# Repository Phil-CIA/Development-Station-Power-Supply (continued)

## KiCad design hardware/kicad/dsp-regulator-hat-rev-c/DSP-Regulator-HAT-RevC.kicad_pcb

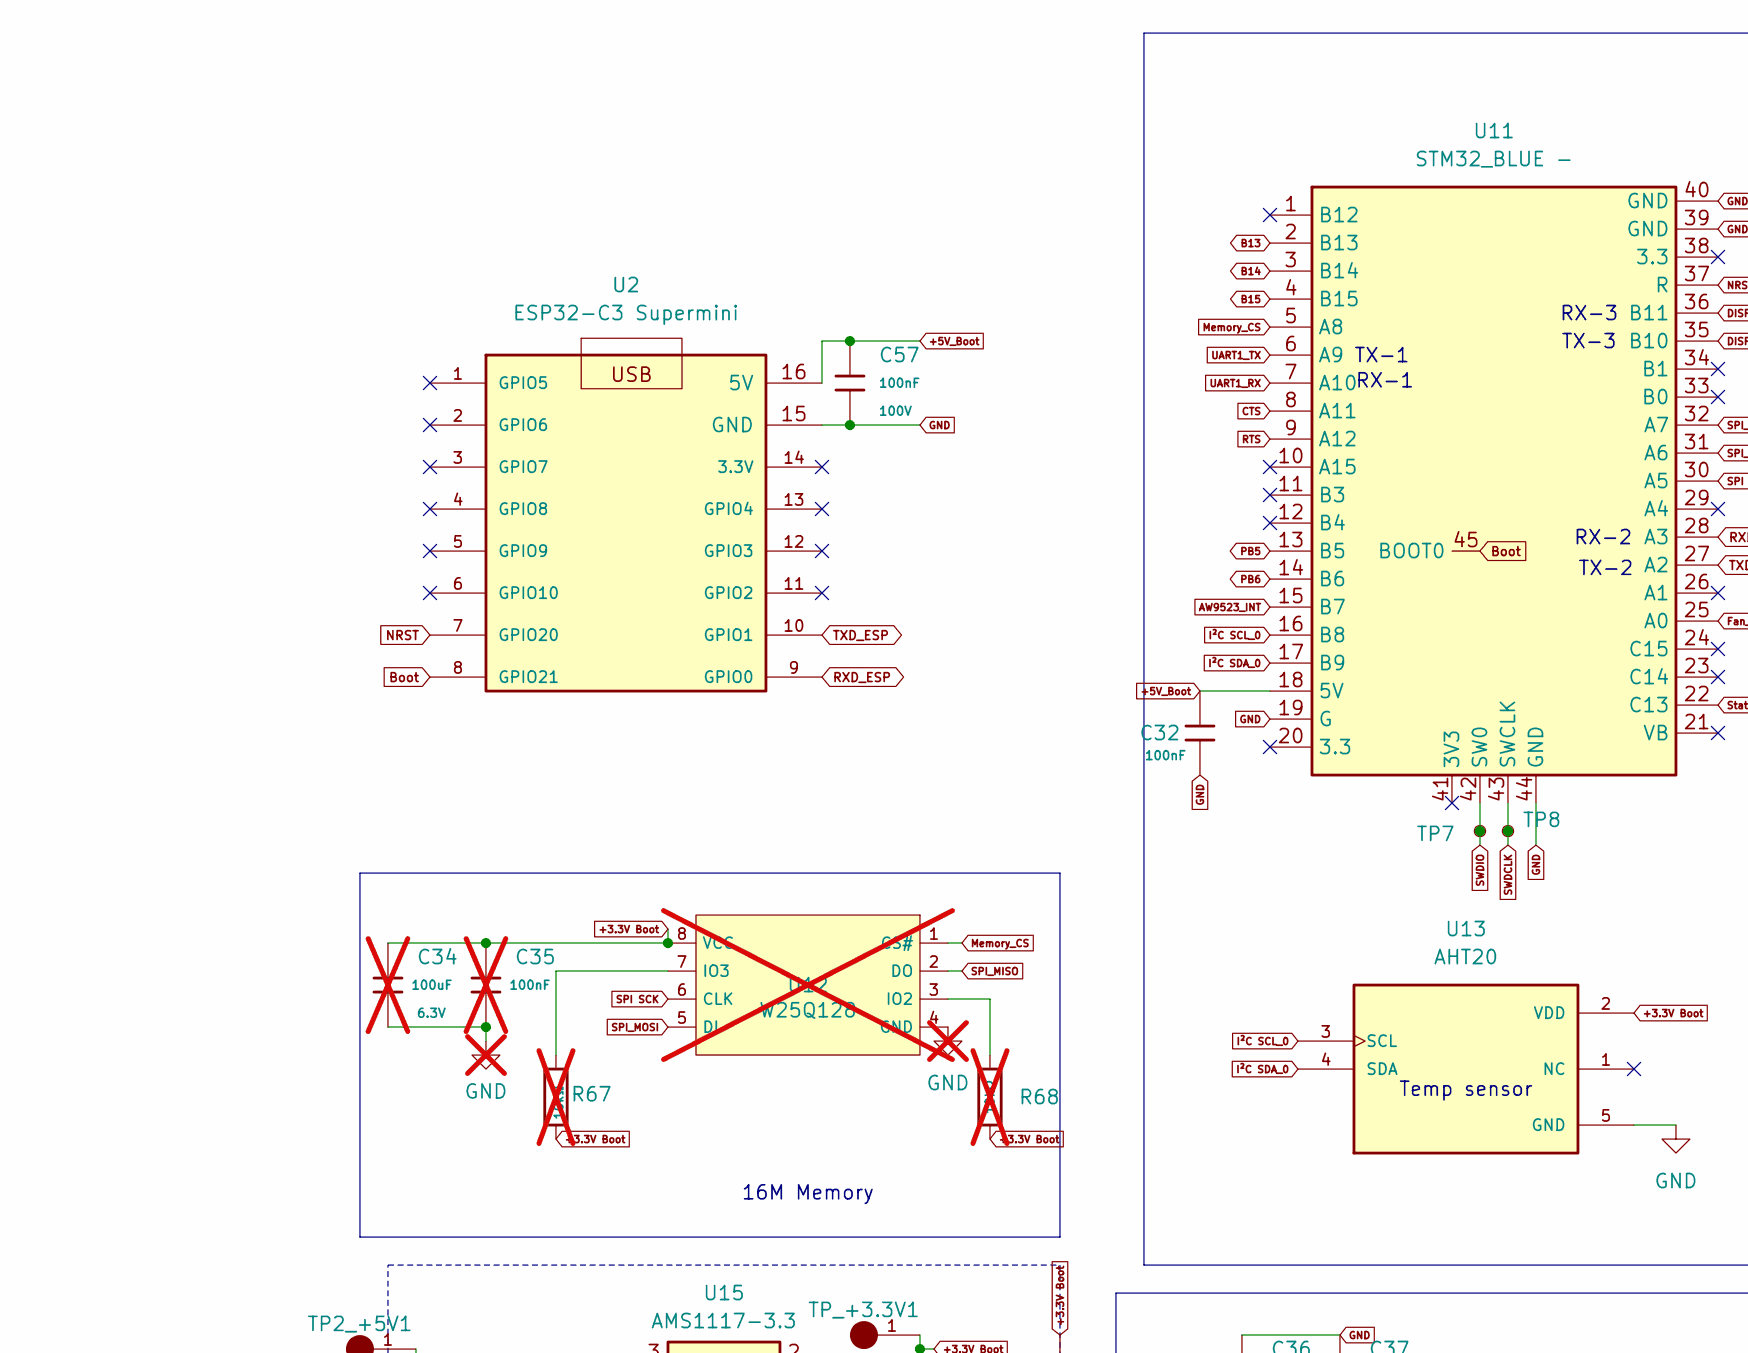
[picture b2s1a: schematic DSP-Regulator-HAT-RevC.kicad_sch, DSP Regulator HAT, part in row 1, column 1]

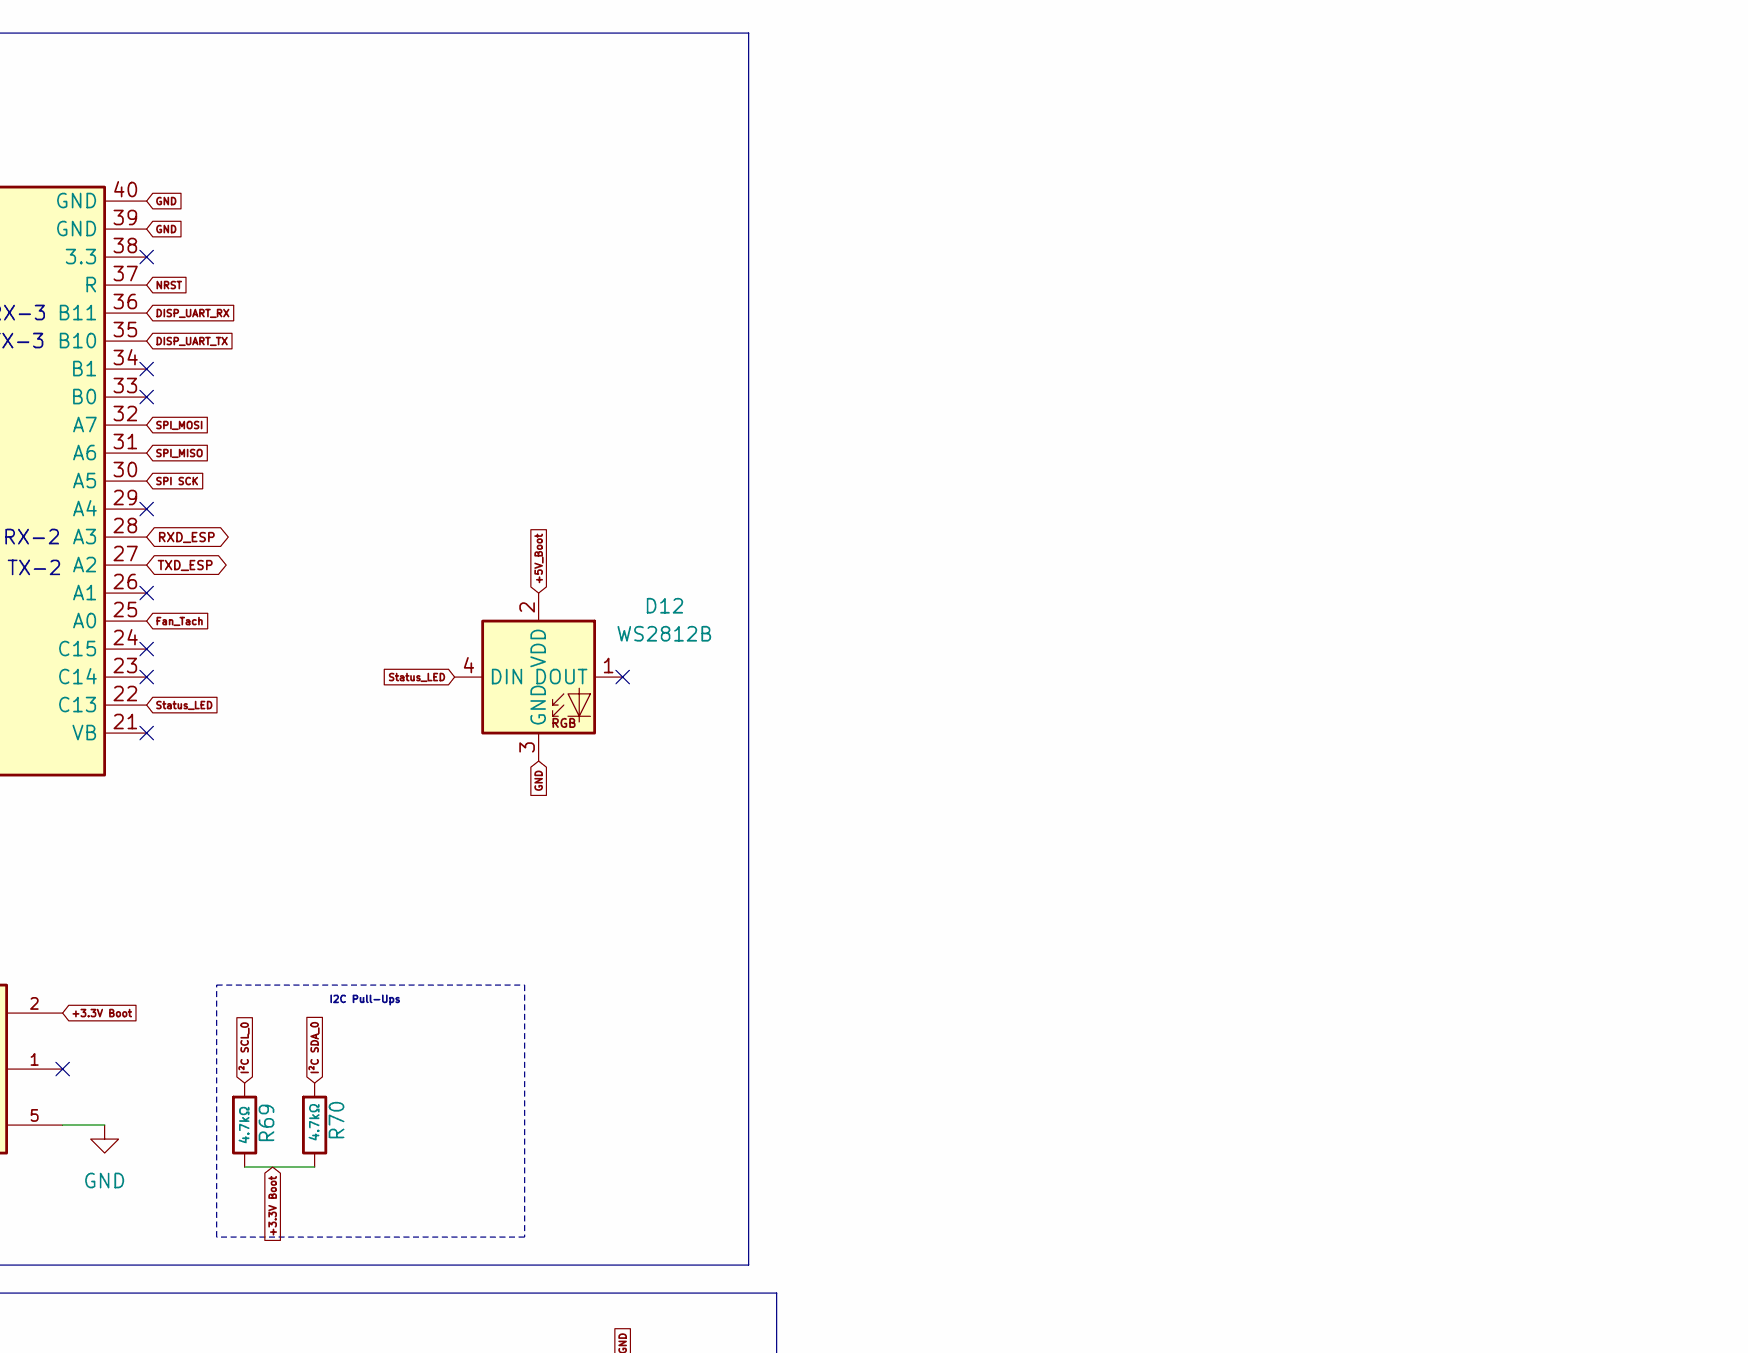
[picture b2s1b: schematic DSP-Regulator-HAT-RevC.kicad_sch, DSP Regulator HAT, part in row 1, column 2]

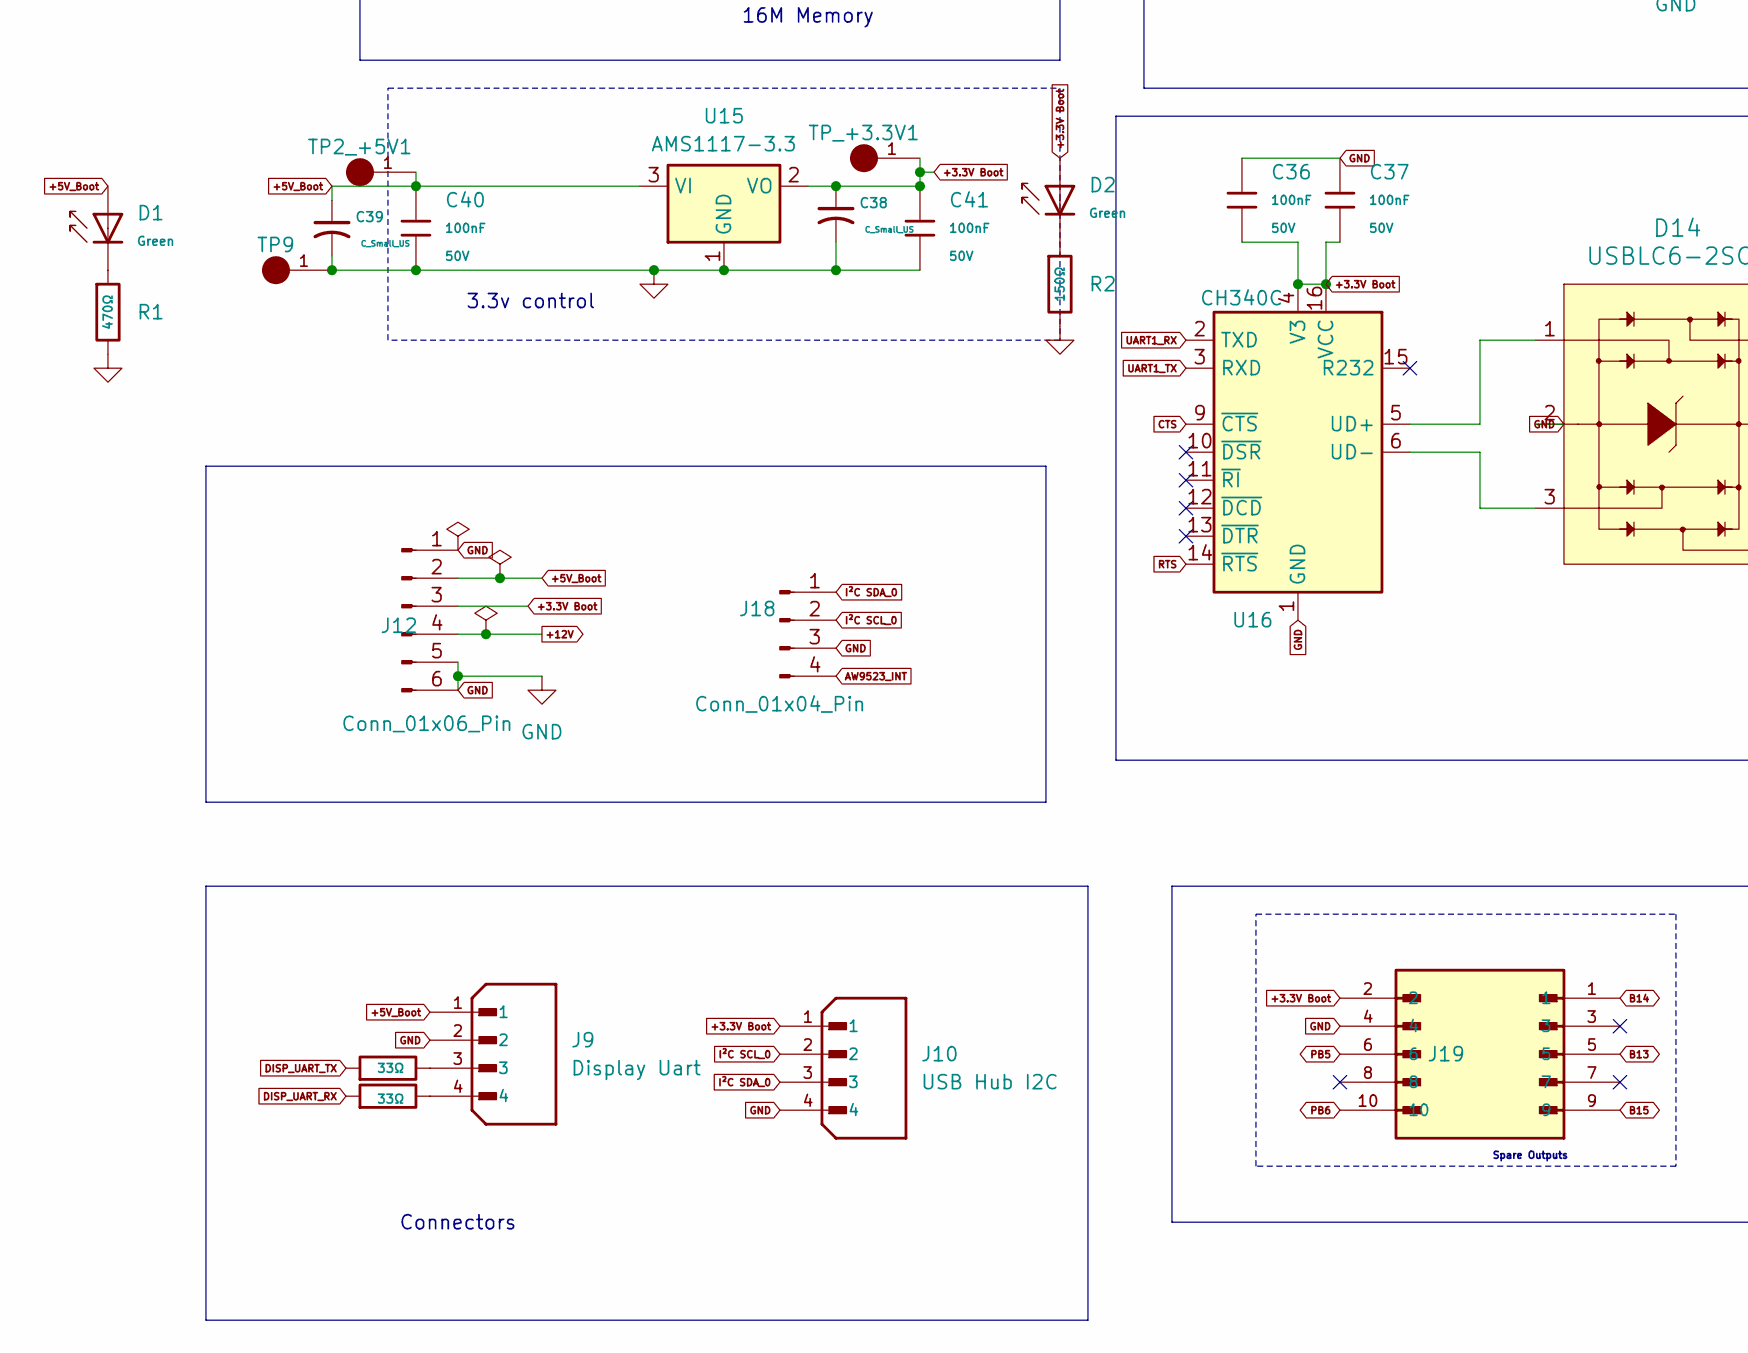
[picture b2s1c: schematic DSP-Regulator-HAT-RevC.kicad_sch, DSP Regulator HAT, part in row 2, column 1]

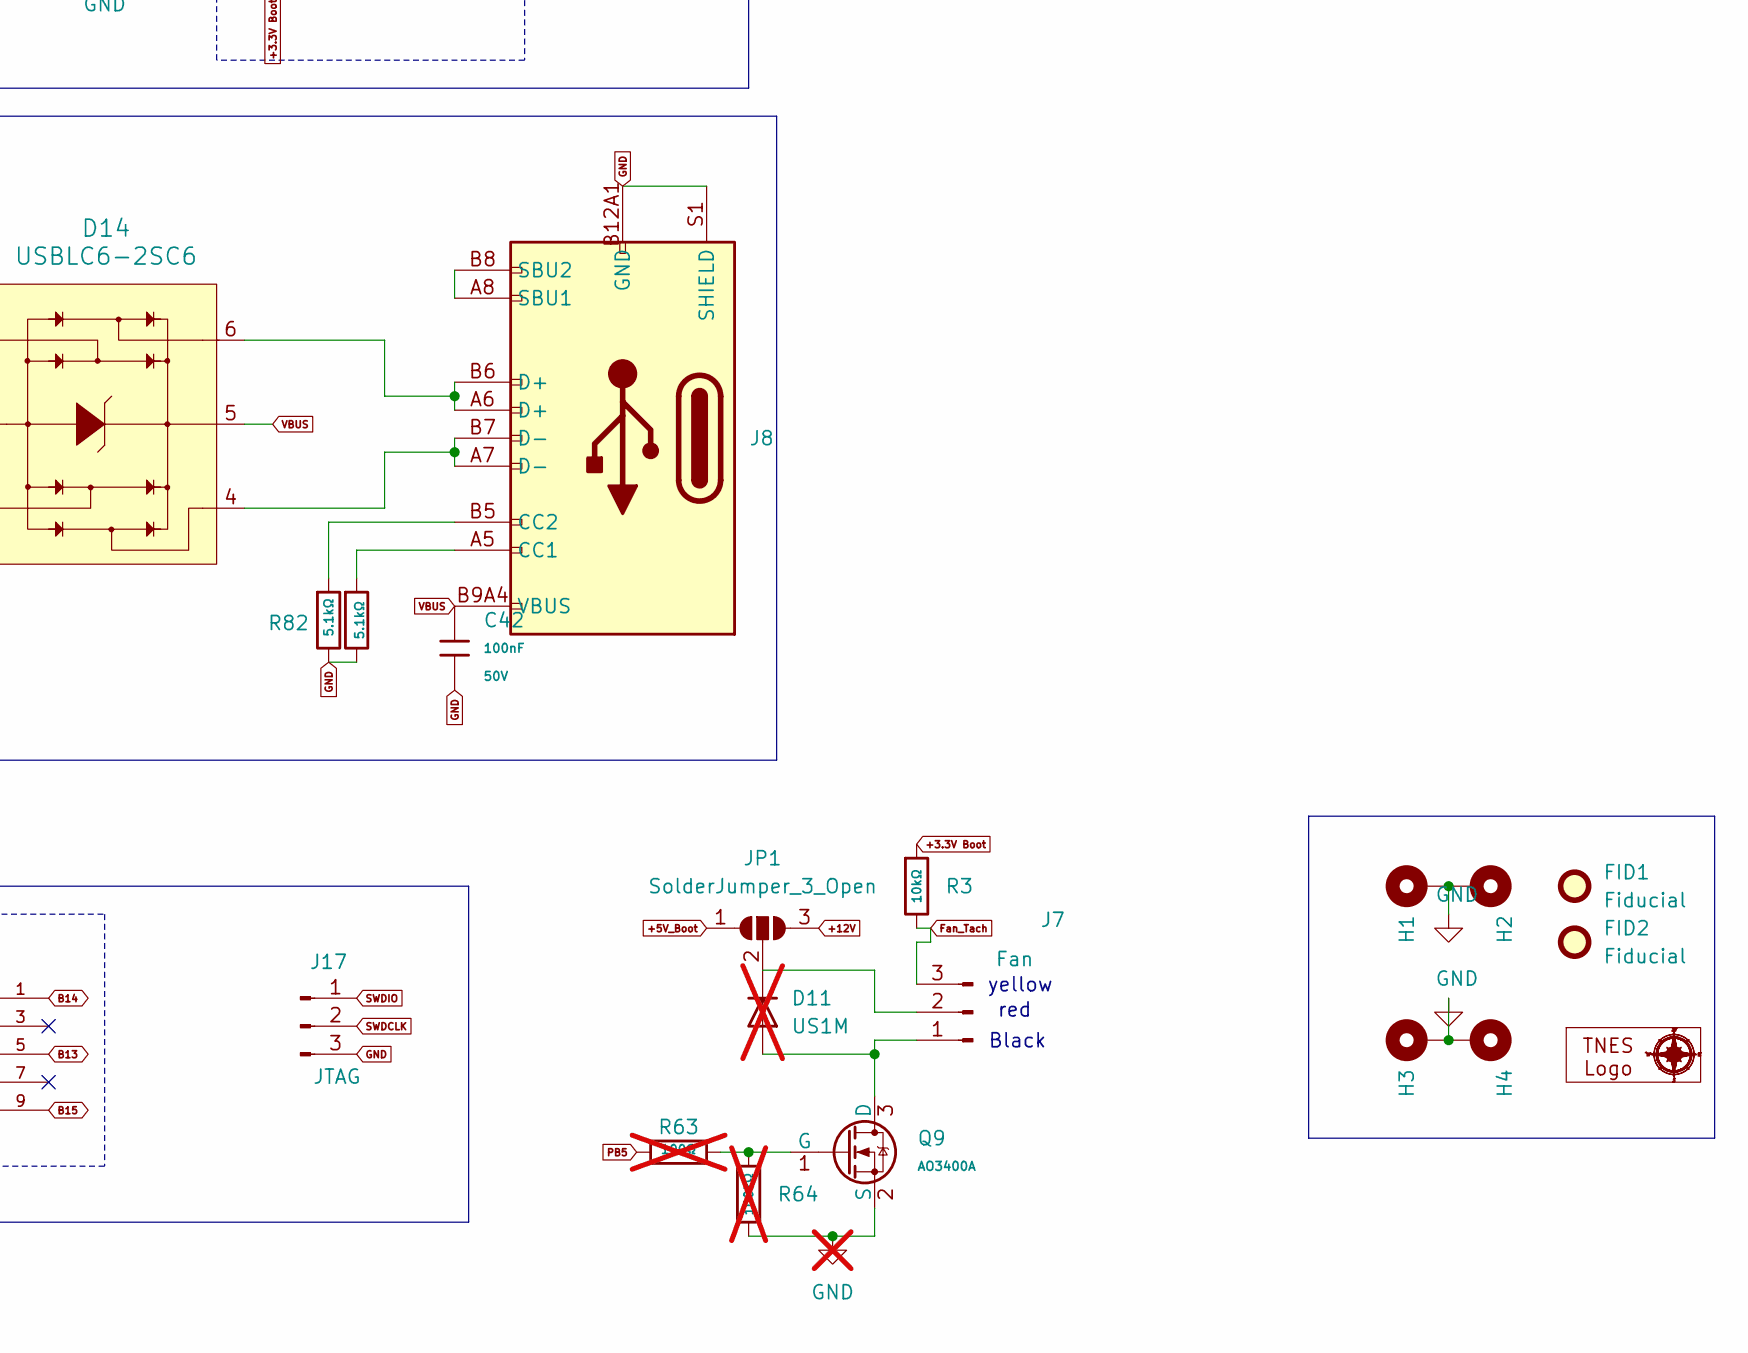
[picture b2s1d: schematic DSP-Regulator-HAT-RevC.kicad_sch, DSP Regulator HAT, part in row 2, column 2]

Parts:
5mm1: 5mm LOGO
C32, C36, C37, C40, C41, C42: 100nF; C_0805; Voltage Rated 50V; Tolerance ±10%; Part CC0805KRX7R9BB104; LCSC C49678
C34: 100uF; C_1206; Voltage Rated 6.3V; Tolerance ±20%; Part CL31A107MQHNNNE; LCSC C15008; not fitted
C35: 100nF; C_0805; Voltage Rated 50V; Tolerance ±10%; Part CC0805KRX7R9BB104; LCSC C49678; not fitted
C38, C39: C_Small_US; CP_Elec_10x10; Part JVE25V470M10X10; LCSC C48615124
C57: 100nF; C_0805; Voltage Rated 100V; Tolerance ±10%; Part CL21B104KCFNNNE; LCSC C28233
D1, D2: Green; D_0805; Part KT-0805G; LCSC C2297
D11: US1M; D_SMA; LCSC C81191; not fitted
D12: WS2812B; LED-SMD_4P-L1.6-W1.5_XL-1615RGBC-WS2812B; LCSC C5349954
D14: USBLC6-2SC6; SOT23-6L; MPN USBLC6-2SC6; Digi-Key_PN 497-5235-1-ND
FID1, FID2: Fiducial; Fiducial_0.75mm_Mask1.5mm
H1, H2, H3, H4: MountingHole_Pad; MountingHole_3.5mm_Pad_Via
J7: Fan; PinHeader_1x03_P2.54mm_Vertical; LCSC C29275
J8: Connector, USB-TYPE-C-16P; TYPE-C-SMD_HX-TYPE-C-16PIN; LCSC C2927039
J9: Display Uart; JST_B4B-XH-A; PARTREV 7/4/21; LCSC C144395
J10: USB Hub I2C; JST_B4B-XH-A; PARTREV 7/4/21; LCSC C144395
J12: Conn_01x06_Pin; PinHeader_1x06_P2.54mm_Vertical; LCSC C492414
J17: JTAG; PinHeader_1x03_P2.54mm_Vertical_SMD_Pin1Right; LCSC C53207560
J18: Conn_01x04_Pin; PinHeader_1x04_P2.54mm_Vertical; LCSC C492412
J19: 20021121-00010C4LF; PinHeader_2x5_P1.27mm; PARTREV S; LCSC C41376037
JP1: SolderJumper_3_Open; SolderJumper-3_P1.3mm_Open_RoundedPad1.0x1.5mm
Q9: AO3400A; Q_SOT-23; Part AO3400A; LCSC C20917
R1: 470Ω; R_0805; Overload Voltage (Max) 150V; Tolerance ±1%; Part 0805W8F4700T5E; LCSC C17710
R2: 150Ω; R_0805; Overload Voltage (Max) 150V; Tolerance ±1%; Part 0805W8F1500T5E; LCSC C17471
R3: 10kΩ; R_0805; Overload Voltage (Max) 150V; Tolerance ±1%; Part 0805W8F1002T5E; LCSC C17414
R63: 100Ω; R_0805; Overload Voltage (Max) 150V; Tolerance ±1%; Part 0805W8F1000T5E; LCSC Part C105588; not fitted
R64: 100kΩ; R_0805; Overload Voltage (Max) 150V; Tolerance ±1%; Part 0805W8F1003T5E; LCSC C149504; not fitted
R67, R68: 10kΩ; R_0805; Overload Voltage (Max) 150V; Tolerance ±1%; Part 0805W8F1002T5E; LCSC C17414; not fitted
R69, R70: 4.7kΩ; R_0805; Overload Voltage (Max) 150V; Tolerance ±1%; Part 0805W8F4701T5E; LCSC C17673
R77, R79: 33Ω; R_0805; Overload Voltage (Max) 150V; Tolerance ±1%; Part 0805W8F330JT5E; LCSC C17634
R82, R83: 5.1kΩ; R_0805; Overload Voltage (Max) 150V; Tolerance ±1%; Part 0805W8F5101T5E; LCSC C27834
TP2_+5V1, TP9: 5015; KEYSTONE_5015; PARTREV F; LCSC C5199798
TP7, TP8: TestPoint_Small; PinHeader_1x01_P1.00mm_Vertical
TP_+3.3V1: 5015; KEYSTONE_5015; PARTREV F; LCSC C5199798
U2: ESP32-C3 Supermini; ESP32 C3 Super Mini; PARTREV 23/05/2022
U11: STM32_BLUE -; STM32 Blue
U12: W25Q128; SOIC-8_L5.3-W5.3-P1.27-LS8.0-BL; Part W25Q128JVSIQ; LCSC C97521; not fitted
U13: AHT20; Humidity sensor; PARTREV V1.0; LCSC Part C2757850
U15: AMS1117-3.3; SOT-223-3_TabPin2; LCSC C6186
U16: CH340C; SOIC-16_3.9x9.9mm_P1.27mm; LCSC C84681

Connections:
+3.3V Boot: C34.1, C35.1, C36.2, C37.2, C38.1, C41.1, D2.2, J10.1, J12.3, J19.2, R3.1, R67.2, R68.2, R69.2, R70.2, TP_+3.3V1.1, U12.8 (VCC), U13.2 (VDD), U15.2 (VO), U16.4 (V3), U16.16 (VCC)
+5V_Boot: C32.1, C39.1, C40.1, C57.1, D1.2, D12.2 (VDD), J9.1, J12.2, JP1.1 (A), TP2_+5V1.1, U2.16 (5V), U11.18 (5V), U15.3 (VI)
+12V: J12.4, JP1.3 (B)
AW9523_INT: J18.4, U11.15 (B7)
B13: J19.5, U11.2 (B13)
B14: J19.1, U11.3 (B14)
B15: J19.9, U11.4 (B15)
Boot: U2.8 (GPIO21), U11.45 (BOOT0)
CTS: U11.8 (A11), U16.9 (~CTS)
DISP_UART_RX: R79.1, U11.36 (B11)
DISP_UART_TX: R77.1, U11.35 (B10)
Fan_Tach: J7.3, R3.2, U11.25 (A0)
GND: C32.2, C34.2, C35.2, C36.1, C37.1, C38.2, C39.2, C40.2, C41.2, C42.2, C57.2, D12.3 (GND), D14.2, H1.1 (1_1), H2.1 (1_1), H3.1 (1_1), H4.1 (1_1), J8.A12B1 (GND), J8.B12A1 (GND), J8.S1 (SHIELD), J9.2, J10.4, J12.1, J12.5, J12.6, J17.3, J18.3, J19.4, Q9.2 (S), R1.2, R2.2, R64.2, R82.2, R83.2, TP9.1, U2.15 (GND), U11.19 (G), U11.39 (GND), U11.40 (GND), U11.44 (GND), U12.4 (GND), U13.5 (GND), U15.1 (GND), U16.1 (GND)
I²C SCL_0: J10.2, J18.2, R69.1, U11.16 (B8), U13.3 (SCL)
I²C SDA_0: J10.3, J18.1, R70.1, U11.17 (B9), U13.4 (SDA)
Memory_CS: U11.5 (A8), U12.1 (CS#)
NRST: U2.7 (GPIO20), U11.37 (R)
unnamed: D1.1, R1.1
unnamed: D2.1, R2.1
unnamed: D11.2 (A), J7.1, Q9.3 (D)
unnamed: D11.1 (K), J7.2, JP1.2 (C)
unnamed: D14.4, J8.A7 (D-), J8.B7 (D-)
unnamed: D14.6, J8.A6 (D+), J8.B6 (D+)
unnamed: J8.A5 (CC1), R83.1
unnamed: J8.B5 (CC2), R82.1
unnamed: J8.A8 (SBU1), J8.B8 (SBU2)
unnamed: J9.3, R77.2
unnamed: J9.4, R79.2
unnamed: Q9.1 (G), R63.2, R64.1
unnamed: R68.1, U12.3 (IO2)
unnamed: R67.1, U12.7 (IO3)
unnamed: D14.1, U16.5 (UD+)
unnamed: D14.3, U16.6 (UD-)
PB5: J19.6, R63.1, U11.13 (B5)
PB6: J19.10, U11.14 (B6)
RTS: U11.9 (A12), U16.14 (~RTS)
RXD_ESP: U2.9 (GPIO0), U11.28 (A3)
SPI SCK: U11.30 (A5), U12.6 (CLK)
SPI_MISO: U11.31 (A6), U12.2 (DO)
SPI_MOSI: U11.32 (A7), U12.5 (DI)
SWDCLK: J17.2, TP8.1 (1_1), U11.43 (SWCLK)
SWDIO: J17.1, TP7.1 (1_1), U11.42 (SW0)
Status_LED: D12.4 (DIN), U11.22 (C13)
TXD_ESP: U2.10 (GPIO1), U11.27 (A2)
UART1_RX: U11.7 (A10), U16.2 (TXD)
UART1_TX: U11.6 (A9), U16.3 (RXD)
VBUS: C42.1, D14.5, J8.A9B4 (VBUS), J8.B9A4 (VBUS)

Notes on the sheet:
RX-3
Connectors
I2C Pull-Ups
Temp sensor
RX-2
red
3.3v control
16M Memory
Spare Outputs
TX-3
TX-2
RX-1
Black
TX-1
yellow

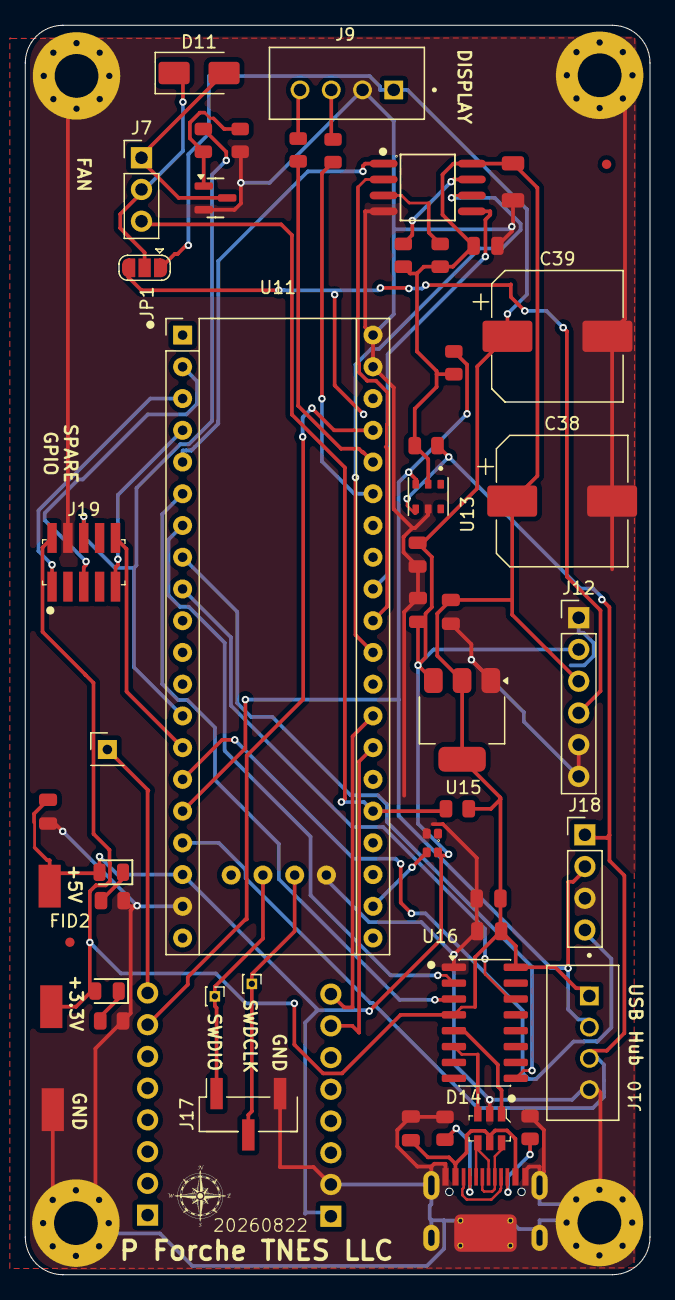
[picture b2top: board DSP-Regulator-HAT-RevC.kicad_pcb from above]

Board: 2 copper layers, 50.0 x 100.0 mm, 57 parts (1 on the bottom side), 47 nets.

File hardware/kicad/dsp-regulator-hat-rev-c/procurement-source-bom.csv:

"Reference","Value","Footprint","LCSC Part #","Manufacturer Part Number","Manufacturer","Datasheet","Qty","DNP"
"5mm1","","1My_Parts_ Passive:5mm LOGO","","","","kicad-embed://Compass-Free-PNG-Image.svg","1",""
"C32","100nF","PCM_JLCPCB:C_0805","C49678","CC0805KRX7R9BB104","YAGEO","https://www.lcsc.com/datasheet/lcsc_datasheet_2304140030_YAG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","1",""
"C34","100uF","PCM_JLCPCB:C_1206","C15008","CL31A107MQHNNNE","Samsung Electro-Mechanics","https://www.lcsc.com/datasheet/lcsc_datasheet_2304140030_Sam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","1","DNP"
"C35","100nF","PCM_JLCPCB:C_0805","C49678","CC0805KRX7R9BB104","YAGEO","https://www.lcsc.com/datasheet/lcsc_datasheet_2304140030_YAG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","1","DNP"
"C36","100nF","PCM_JLCPCB:C_0805","C49678","CC0805KRX7R9BB104","YAGEO","https://www.lcsc.com/datasheet/lcsc_datasheet_2304140030_YAG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","1",""
"C37","100nF","PCM_JLCPCB:C_0805","C49678","CC0805KRX7R9BB104","YAGEO","https://www.lcsc.com/datasheet/lcsc_datasheet_2304140030_YAG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","1",""
"C38","C_Small_US","Capacitor_SMD:CP_Elec_10x10","C48615124","JVE25V470M10X10","","","1",""
"C39","C_Small_US","Capacitor_SMD:CP_Elec_10x10","C48615124","JVE25V470M10X10","","","1",""
"C40","100nF","PCM_JLCPCB:C_0805","C49678","CC0805KRX7R9BB104","YAGEO","https://www.lcsc.com/datasheet/lcsc_datasheet_2304140030_YAG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","1",""
"C41","100nF","PCM_JLCPCB:C_0805","C49678","CC0805KRX7R9BB104","YAGEO","https://www.lcsc.com/datasheet/lcsc_datasheet_2304140030_YAG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","1",""
"C42","100nF","PCM_JLCPCB:C_0805","C49678","CC0805KRX7R9BB104","YAGEO","https://www.lcsc.com/datasheet/lcsc_datasheet_2304140030_YAG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","1",""
"C57","100nF","PCM_JLCPCB:C_0805","C28233","CL21B104KCFNNNE","Samsung Electro-Mechanics","https://www.lcsc.com/datasheet/lcsc_datasheet_2304140030_Sam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","1",""
"D1","Green","PCM_JLCPCB:D_0805","C2297","KT-0805G","Hubei KENTO Elec","https://www.lcsc.com/datasheet/lcsc_datasheet_1806151820_Hub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","1",""
"D2","Green","PCM_JLCPCB:D_0805","C2297","KT-0805G","Hubei KENTO Elec","https://www.lcsc.com/datasheet/lcsc_datasheet_1806151820_Hub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","1",""
"D11","US1M","Diode_SMD:D_SMA","C81191","","","https://www.lcsc.com/datasheet/C81191.pdf?spm=wm.sxq.inf.ggs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","1","DNP"
"D12","WS2812B","PCM_JLCPCB:LED-SMD_4P-L1.6-W1.5_XL-1615RGBC-WS2812B","C5349954","","","https://atta.szlcsc.com/upload/public/pdf/source/20230111/5A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","1",""
"D14","USBLC6-2SC6","digikey-footprints:SOT23-6L","C7519","","STMicroelectronics","http://www.st.com/content/ccc/resource/technical/document/da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","1",""
"J7","Fan","Connector_PinHeader_2.54mm:PinHeader_1x03_P2.54mm_Vertical","C29275","","","https://www.lcsc.com/datasheet/C29275.pdf?spm=wm.sxq.inf.ggs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","1",""
"J8","Connector, USB-TYPE-C-16P","PCM_JLCPCB:TYPE-C-SMD_HX-TYPE-C-16PIN","C2927039","","","https://atta.szlcsc.com/upload/public/pdf/source/20220920/0E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","1",""
"J9","Display Uart","1My_Parts_ Connectors:JST_B4B-XH-A","C144395","","","","1",""
"J10","USB Hub I2C","1My_Parts_ Connectors:JST_B4B-XH-A","C144395","","","","1",""
"J12","Conn_01x06_Pin","Connector_PinHeader_2.54mm:PinHeader_1x06_P2.54mm_Vertical","C492414","","","https://www.lcsc.com/datasheet/C492414.pdf?spm=wm.sxq.inf.gg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","1",""
"J17","JTAG","Connector_PinHeader_2.54mm:PinHeader_1x03_P2.54mm_Vertical_SMD_Pin1Right","C53207560","","","https://www.lcsc.com/datasheet/C53207560.pdf?spm=wm.sxq.inf.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","1",""
"J18","Conn_01x04_Pin","Connector_PinHeader_2.54mm:PinHeader_1x04_P2.54mm_Vertical","C492412","","","https://www.lcsc.com/datasheet/C492412.pdf?spm=wm.sxq.inf.gg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","1",""
"J19","20021121-00010C4LF","digikey-footprints:PinHeader_2x5_P1.27mm"," C41376037","","","","1",""
"Q9","AO3400A","PCM_JLCPCB:Q_SOT-23","C20917","AO3400A","Alpha & Omega Semicon","https://www.lcsc.com/datasheet/lcsc_datasheet_1811081213_Alp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","1",""
"R1","470Ω","PCM_JLCPCB:R_0805","C17710","0805W8F4700T5E","UNI-ROYAL(Uniroyal Elec)","https://www.lcsc.com/datasheet/lcsc_datasheet_2206010200_UNI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","1",""
"R2","150Ω","PCM_JLCPCB:R_0805","C17471","0805W8F1500T5E","UNI-ROYAL(Uniroyal Elec)","https://www.lcsc.com/datasheet/lcsc_datasheet_2206010216_UNI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","1",""
"R3","10kΩ","PCM_JLCPCB:R_0805","C17414","0805W8F1002T5E","UNI-ROYAL(Uniroyal Elec)","https://www.lcsc.com/datasheet/lcsc_datasheet_2411221126_UNI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","1",""
"R63","100Ω","PCM_JLCPCB:R_0805","C17408","0805W8F1000T5E","UNI-ROYAL(Uniroyal Elec)","https://www.lcsc.com/datasheet/lcsc_datasheet_2411221126_UNI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","1","DNP"
"R64","100kΩ","PCM_JLCPCB:R_0805","C149504","0805W8F1003T5E","UNI-ROYAL(Uniroyal Elec)","https://www.lcsc.com/datasheet/lcsc_datasheet_2205312316_UNI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","1","DNP"
"R67","10kΩ","PCM_JLCPCB:R_0805","C17414","0805W8F1002T5E","UNI-ROYAL(Uniroyal Elec)","https://www.lcsc.com/datasheet/lcsc_datasheet_2411221126_UNI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","1","DNP"
"R68","10kΩ","PCM_JLCPCB:R_0805","C17414","0805W8F1002T5E","UNI-ROYAL(Uniroyal Elec)","https://www.lcsc.com/datasheet/lcsc_datasheet_2411221126_UNI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","1","DNP"
"R69","4.7kΩ","PCM_JLCPCB:R_0805","C17673","0805W8F4701T5E","UNI-ROYAL(Uniroyal Elec)","https://www.lcsc.com/datasheet/lcsc_datasheet_2206010200_UNI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","1",""
"R70","4.7kΩ","PCM_JLCPCB:R_0805","C17673","0805W8F4701T5E","UNI-ROYAL(Uniroyal Elec)","https://www.lcsc.com/datasheet/lcsc_datasheet_2206010200_UNI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","1",""
"R77","33Ω","PCM_JLCPCB:R_0805","C17634","0805W8F330JT5E","UNI-ROYAL(Uniroyal Elec)","https://www.lcsc.com/datasheet/lcsc_datasheet_2205311830_UNI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","1",""
"R79","33Ω","PCM_JLCPCB:R_0805","C17634","0805W8F330JT5E","UNI-ROYAL(Uniroyal Elec)","https://www.lcsc.com/datasheet/lcsc_datasheet_2205311830_UNI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","1",""
"R82","5.1kΩ","PCM_JLCPCB:R_0805","C27834","0805W8F5101T5E","UNI-ROYAL(Uniroyal Elec)","https://www.lcsc.com/datasheet/lcsc_datasheet_2206010030_UNI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","1",""
"R83","5.1kΩ","PCM_JLCPCB:R_0805","C27834","0805W8F5101T5E","UNI-ROYAL(Uniroyal Elec)","https://www.lcsc.com/datasheet/lcsc_datasheet_2206010030_UNI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","1",""
"TP2_+5V1","5015","1My_Parts_ Connectors:KEYSTONE_5015","C5199798","","","","1",""
"TP7","TestPoint_Small","Connector_PinHeader_1.00mm:PinHeader_1x01_P1.00mm_Vertical","","","","","1",""
"TP8","TestPoint_Small","Connector_PinHeader_1.00mm:PinHeader_1x01_P1.00mm_Vertical","","","","","1",""
"TP9","5015","1My_Parts_ Connectors:KEYSTONE_5015","C5199798","","","","1",""
"TP_+3.3V1","5015","1My_Parts_ Connectors:KEYSTONE_5015","C5199798","","","","1",""
"U2","ESP32-C3 Supermini","1My_Parts_ MPUs:ESP32 C3 Super Mini","","","","","1",""
"U11","STM32_BLUE -","1My_Parts_ MPUs:STM32 Blue","","","","https://stm32-base.org/assets/pdf/boards/original-schematic-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","1",""
"U12","W25Q128","PCM_JLCPCB:SOIC-8_L5.3-W5.3-P1.27-LS8.0-BL","C97521","W25Q128JVSIQ","Winbond Elec","https://www.lcsc.com/datasheet/lcsc_datasheet_1811142111_Win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","1","DNP"
"U13","AHT20","1My_Parts_ ICs:Humidity sensor","C2757850","","","https://www.lcsc.com/datasheet/C2757850.pdf?spm=wm.sxq.inf.g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","1",""
"U15","AMS1117-3.3","Package_TO_SOT_SMD:SOT-223-3_TabPin2","C6186","","","http://www.advanced-monolithic.com/pdf/ds1117.pdf","1",""
"U16","CH340C","Package_SO:SOIC-16_3.9x9.9mm_P1.27mm","C84681","","","https://www.lcsc.com/datasheet/C84681.pdf","1",""
